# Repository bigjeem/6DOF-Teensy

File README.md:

# 6DOF-Teensy
6 DOF Servo Controller using a Teensy4.1

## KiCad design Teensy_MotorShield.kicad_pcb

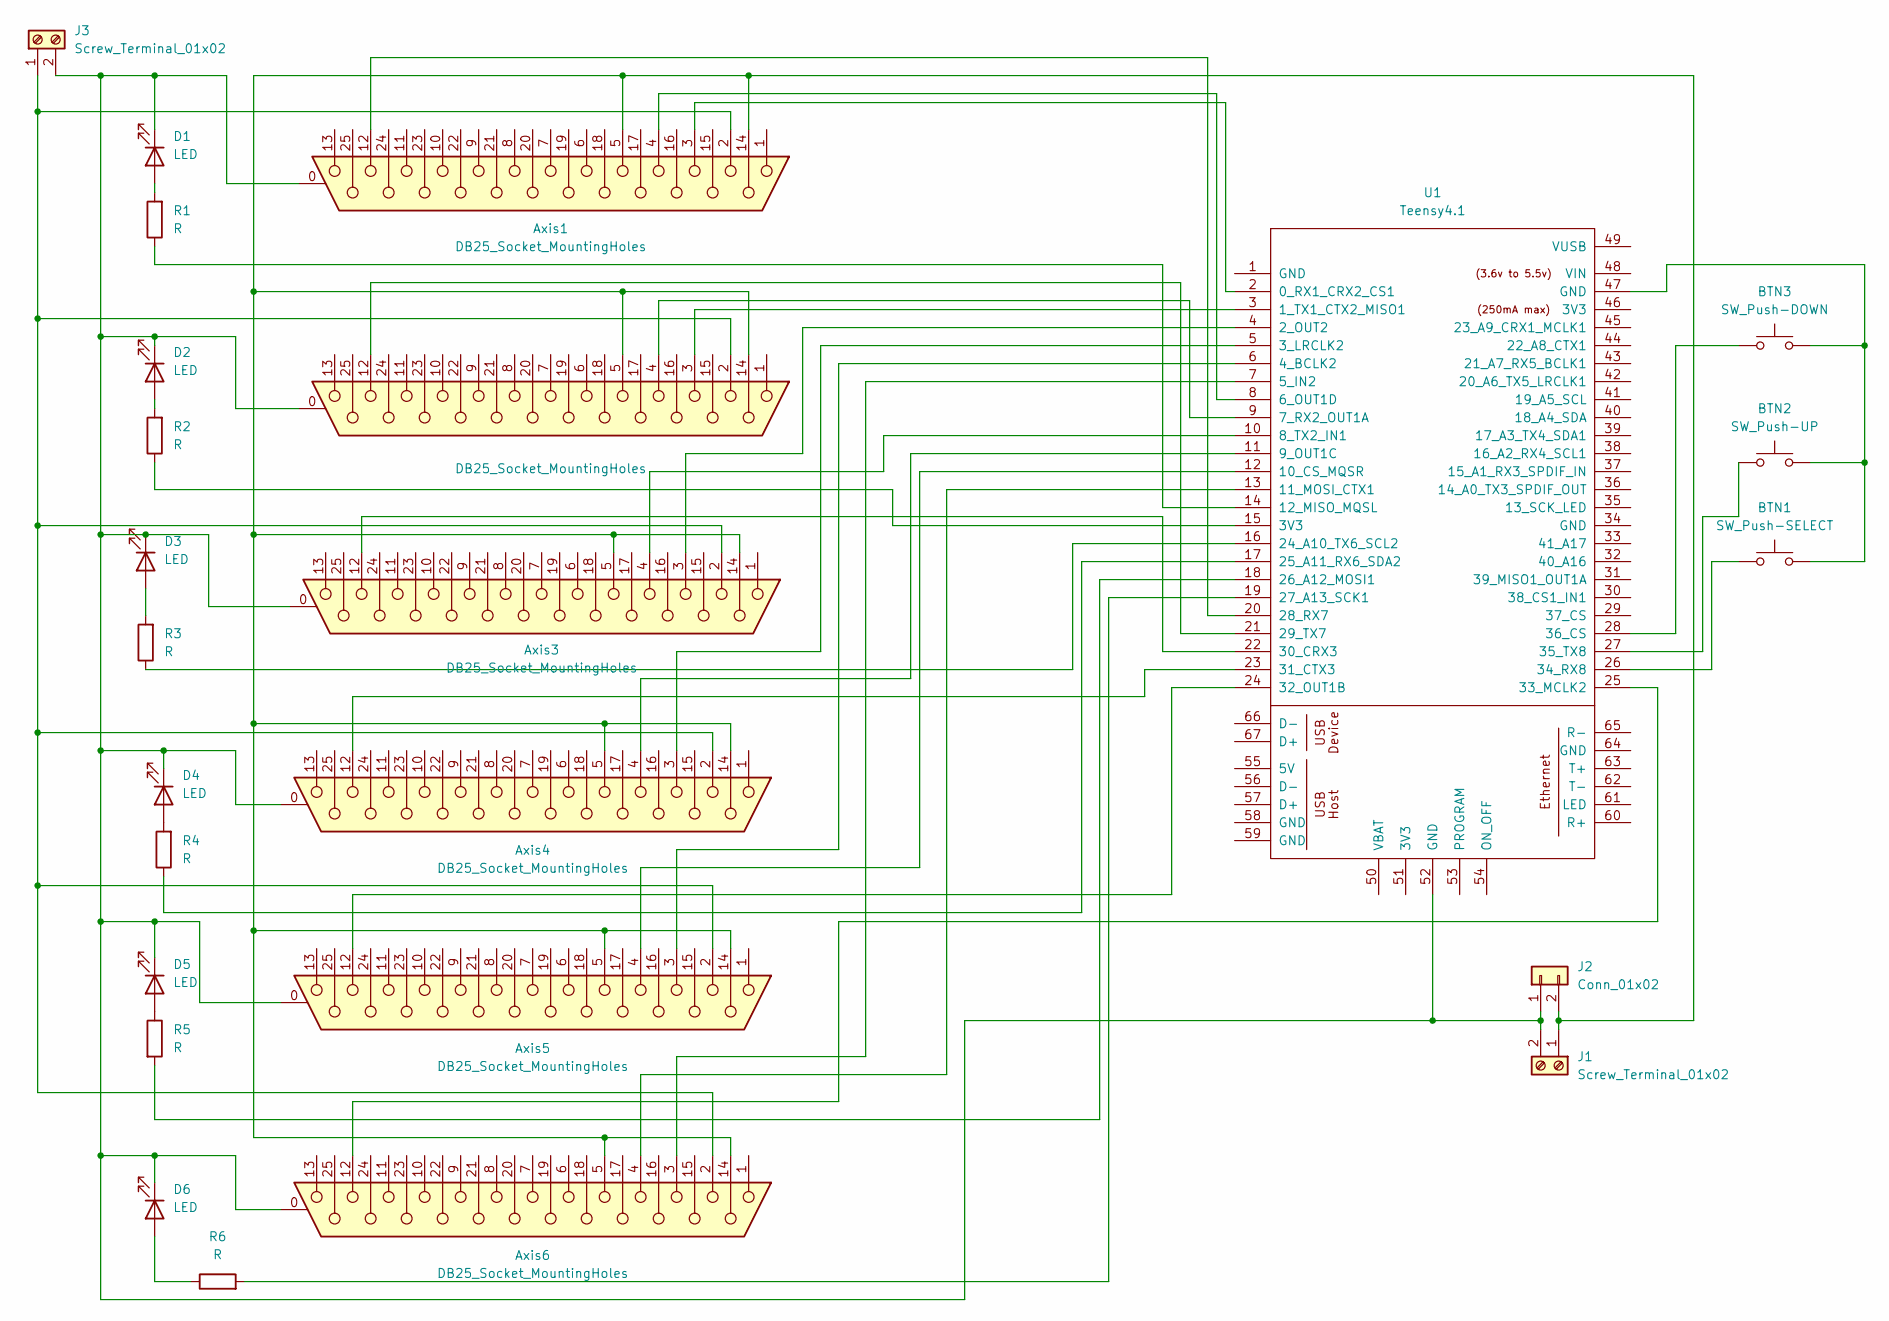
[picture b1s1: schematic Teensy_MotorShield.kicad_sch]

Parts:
Axis1, Axis2, Axis3, Axis4, Axis5, Axis6: DB25_Socket_MountingHoles; DSUB-25_Socket_Vertical_P2.77x2.84mm_MountingHoles
BTN1: SW_Push-SELECT; SW_PUSH_6mm_H7.3mm
BTN2: SW_Push-UP; SW_PUSH_6mm_H7.3mm
BTN3: SW_Push-DOWN; SW_PUSH_6mm_H7.3mm
D1, D2, D3, D4, D5, D6: LED; LED_D3.0mm
J1, J3: Screw_Terminal_01x02; TerminalBlock_Phoenix_MKDS-3-2-5.08_1x02_P5.08mm_Horizontal
J2: Conn_01x02; PinHeader_1x02_P2.54mm_Vertical
R1, R2, R3, R4, R5, R6: R; R_1206_3216Metric_Pad1.30x1.75mm_HandSolder
U1: Teensy4.1; Teensy41

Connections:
unnamed: Axis1.5, Axis1.14, Axis2.5, Axis2.14, Axis3.5, Axis3.14, Axis4.5, Axis4.14, Axis5.5, Axis5.14, Axis6.5, Axis6.14, J1.1, J2.2
unnamed: Axis1.0 (PAD), Axis2.0 (PAD), Axis3.0 (PAD), Axis4.0 (PAD), Axis5.0 (PAD), Axis6.0 (PAD), D1.1 (K), D2.1 (K), D3.1 (K), D4.1 (K), D5.1 (K), D6.1 (K), J1.2, J2.1, J3.2, U1.52 (GND)
unnamed: BTN1.2, BTN2.2, BTN3.2, U1.47 (GND)
unnamed: D1.2 (A), R1.2
unnamed: D2.2 (A), R2.2
unnamed: D3.2 (A), R3.2
unnamed: D4.2 (A), R4.2
unnamed: D5.2 (A), R5.1
unnamed: D6.2 (A), R6.1
unnamed: Axis1.2, Axis2.2, Axis3.2, Axis4.2, Axis5.2, Axis6.2, J3.1
unnamed: R2.1, U1.15 (3V3)
unnamed: Axis1.3, U1.2 (0_RX1_CRX2_CS1)
unnamed: Axis2.3, U1.3 (1_TX1_CTX2_MISO1)
unnamed: Axis3.3, U1.4 (2_OUT2)
unnamed: Axis4.3, U1.5 (3_LRCLK2)
unnamed: Axis5.3, U1.6 (4_BCLK2)
unnamed: Axis6.3, U1.7 (5_IN2)
unnamed: Axis1.4, U1.8 (6_OUT1D)
unnamed: Axis2.4, U1.9 (7_RX2_OUT1A)
unnamed: Axis3.4, U1.10 (8_TX2_IN1)
unnamed: Axis4.4, U1.11 (9_OUT1C)
unnamed: Axis5.4, U1.12 (10_CS_MQSR)
unnamed: Axis6.4, U1.13 (11_MOSI_CTX1)
unnamed: R1.1, U1.14 (12_MISO_MQSL)
unnamed: R3.1, U1.16 (24_A10_TX6_SCL2)
unnamed: R4.1, U1.17 (25_A11_RX6_SDA2)
unnamed: R5.2, U1.18 (26_A12_MOSI1)
unnamed: R6.2, U1.19 (27_A13_SCK1)
unnamed: Axis1.12, U1.20 (28_RX7)
unnamed: Axis2.12, U1.21 (29_TX7)
unnamed: Axis3.12, U1.22 (30_CRX3)
unnamed: Axis4.12, U1.23 (31_CTX3)
unnamed: Axis5.12, U1.24 (32_OUT1B)
unnamed: Axis6.12, U1.25 (33_MCLK2)
unnamed: BTN1.1, U1.26 (34_RX8)
unnamed: BTN2.1, U1.27 (35_TX8)
unnamed: BTN3.1, U1.28 (36_CS)

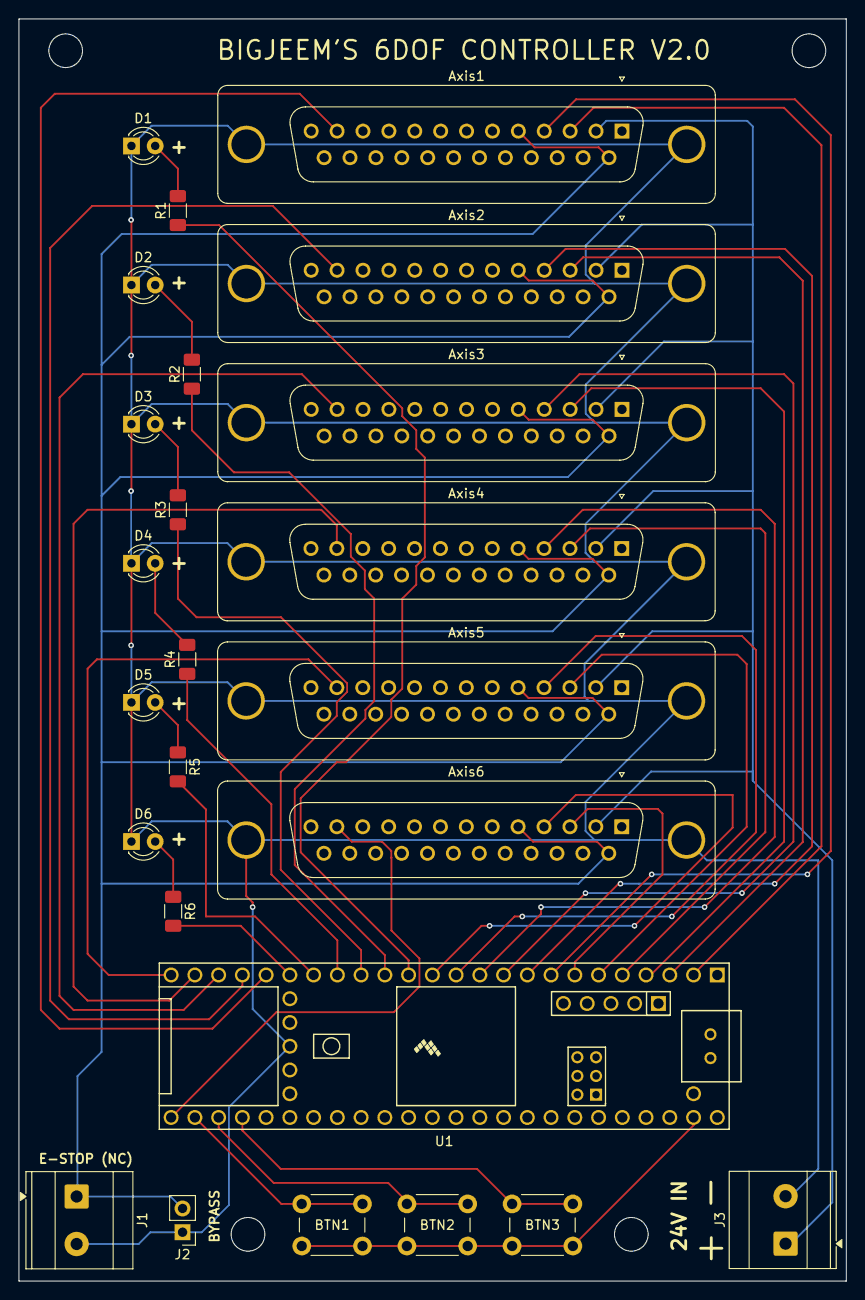
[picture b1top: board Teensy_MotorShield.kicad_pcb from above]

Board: 2 copper layers, 88.5 x 135.0 mm, 25 parts (0 on the bottom side), 37 nets.
